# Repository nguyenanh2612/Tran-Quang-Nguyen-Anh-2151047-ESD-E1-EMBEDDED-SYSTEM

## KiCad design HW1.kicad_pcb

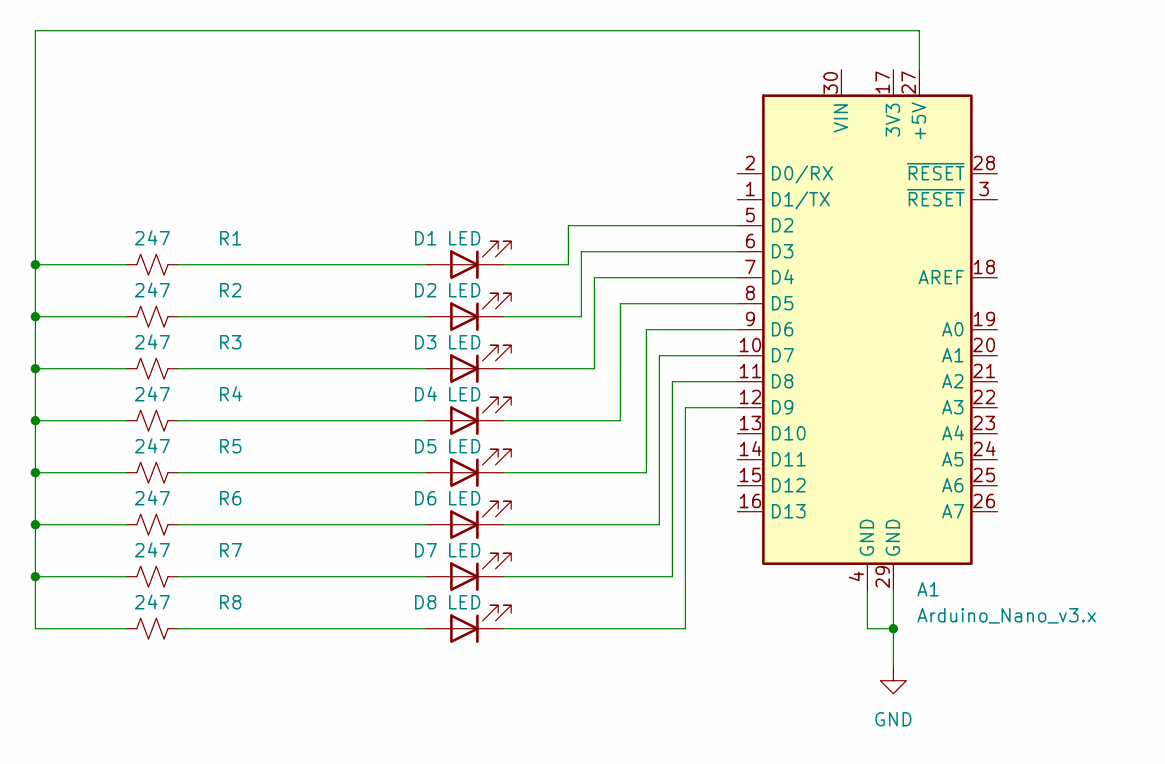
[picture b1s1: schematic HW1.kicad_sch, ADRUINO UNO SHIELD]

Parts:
A1: Arduino_Nano_v3.x; Arduino_Nano
D1, D2, D3, D4, D5, D6, D7, D8: LED; LED_0805_2012Metric
R1, R2, R3, R4, R5, R6, R7, R8: 247; R_0603_1608Metric

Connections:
GND: A1.4 (GND), A1.29 (GND)
unnamed: A1.27 (+5V), R1.1, R2.1, R3.1, R4.1, R5.1, R6.1, R7.1, R8.1
unnamed: A1.5 (D2), D1.1 (K)
unnamed: A1.6 (D3), D2.1 (K)
unnamed: A1.7 (D4), D3.1 (K)
unnamed: A1.8 (D5), D4.1 (K)
unnamed: A1.9 (D6), D5.1 (K)
unnamed: A1.10 (D7), D6.1 (K)
unnamed: A1.11 (D8), D7.1 (K)
unnamed: A1.12 (D9), D8.1 (K)
unnamed: D1.2 (A), R1.2
unnamed: D2.2 (A), R2.2
unnamed: D3.2 (A), R3.2
unnamed: D4.2 (A), R4.2
unnamed: D5.2 (A), R5.2
unnamed: D6.2 (A), R6.2
unnamed: D7.2 (A), R7.2
unnamed: D8.2 (A), R8.2

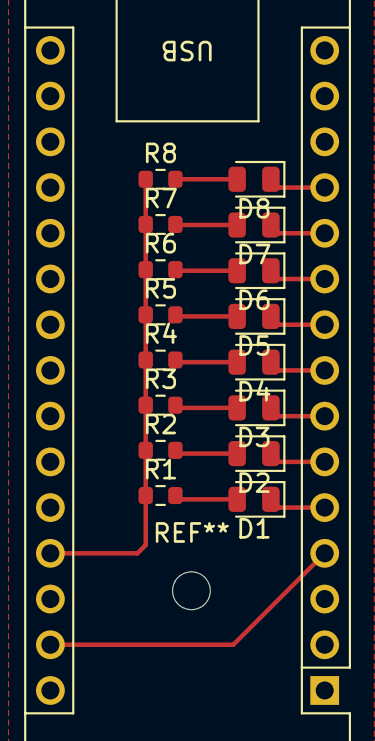
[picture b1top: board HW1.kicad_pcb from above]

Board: 2 copper layers, 17 parts (0 on the bottom side), 18 nets.
